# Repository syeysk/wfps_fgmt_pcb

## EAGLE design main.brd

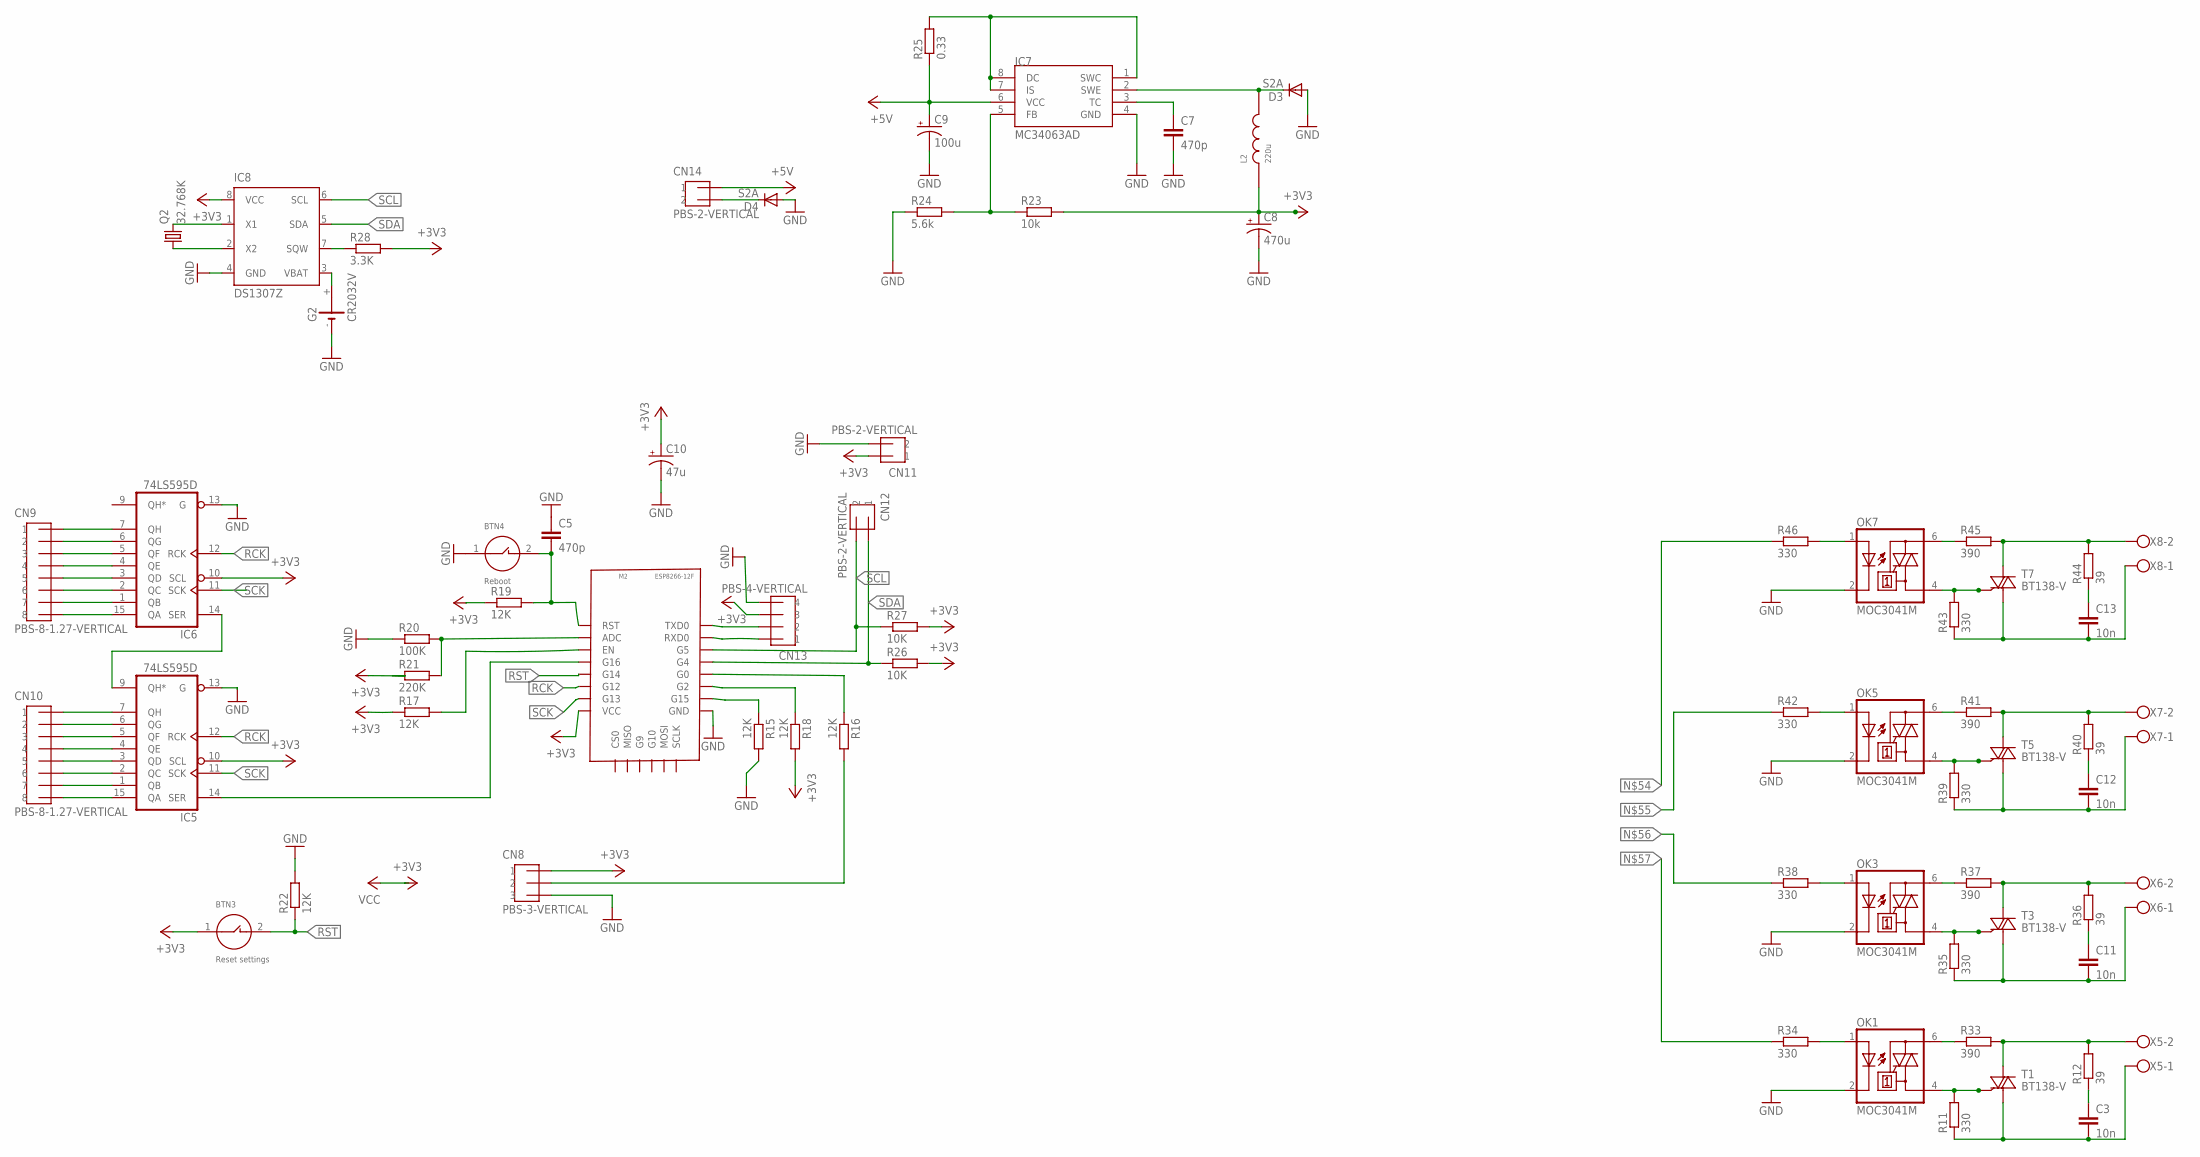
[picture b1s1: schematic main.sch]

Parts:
BTN3: Reset settings; BTN-6X4-SMD
BTN4: Reboot; BTN-6X4-SMD
C3, C11, C12, C13: 10n; C10B5
C5, C7: 470p; C0603
C8: 470u; D/7343-31W
C9: 100u; D/7343-31W
C10: 47u; CT3216
CN8: PBS-3-VERTICAL
CN9, CN10: PBS-8-1.27-VERTICAL
CN11, CN12, CN14: PBS-2-VERTICAL
CN13: PBS-4-VERTICAL
D3, D4: S2A; DO214AA
G2: CR2032V
IC5, IC6: 74LS595D; SO16
IC7: MC34063AD; SOIC8
IC8: DS1307Z; SOIC8
L2: 220u; INDUCTOR-5-10
M2: ESP8266-12F
OK1, OK3, OK5, OK7: MOC3041M; DIL06
Q2: 32.768K; TC38H
R11, R35, R39, R43: 330; 0411/12
R12, R36, R40, R44: 39; 0411/12
R15, R16, R17, R18, R19, R22: 12K; R0603
R20: 100K; R0603
R21: 220K; R0603
R23: 10k; R0603
R24: 5.6k; R0603
R25: 0.33; R0603
R26, R27: 10K; R0603
R28: 3.3K; R0603
R33, R37, R41, R45: 390; 0411/12
R34, R38, R42, R46: 330; R0603
T1, T3, T5, T7: BT138-V; TO220BV
X5, X6, X7, X8: W237-102

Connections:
+3V3: BTN3.1, C8.+, C10.- (+), CN8.P$1 (1), CN11.P$1 (1), CN13.P$3 (3), IC5.10 (SCL), IC5.16 (VCC), IC6.10 (SCL), IC6.16 (VCC), IC8.8 (VCC), L2.P$1 (1), M2.VCC, R17.1, R18.2, R19.1, R21.1, R23.2, R26.2, R27.2, R28.2
+5V: C9.+, CN14.P$1 (1), IC7.6 (VCC), R25.1
GND: BTN4.1, C5.1, C7.2, C8.-, C9.-, C10.+ (-), CN8.P$3 (3), CN11.P$2 (2), CN13.P$4 (4), D3.A, D4.A, G2.-, IC5.8 (GND), IC5.13 (G), IC6.8 (GND), IC6.13 (G), IC7.4 (GND), IC8.4 (GND), M2.GND, OK1.2 (C), OK3.2 (C), OK5.2 (C), OK7.2 (C), R15.2, R20.1, R22.2, R24.1
unnamed: OK1.1 (A), R34.2
unnamed: OK1.6 (A2), R33.1
unnamed: OK1.4 (A1), R11.2, T1.G
unnamed: R12.2, R33.2, T1.T2 (A2), X5.2
unnamed: C3.2, R11.1, T1.T1 (A1), X5.1
unnamed: C3.1, R12.1
unnamed: OK3.1 (A), R38.2
unnamed: M2.G15, R15.1
unnamed: M2.G2, R18.1
unnamed: M2.G0, R16.1
unnamed: CN8.P$2 (2), R16.2
unnamed: M2.EN, R17.2
unnamed: CN9.P$1 (1), IC6.7 (QH)
unnamed: CN9.P$2 (2), IC6.6 (QG)
unnamed: CN9.P$3 (3), IC6.5 (QF)
unnamed: CN9.P$4 (4), IC6.4 (QE)
unnamed: CN9.P$5 (5), IC6.3 (QD)
unnamed: CN9.P$6 (6), IC6.2 (QC)
unnamed: CN9.P$7 (7), IC6.1 (QB)
unnamed: CN9.P$8 (8), IC6.15 (QA)
unnamed: CN10.P$1 (1), IC5.7 (QH)
unnamed: CN10.P$2 (2), IC5.6 (QG)
unnamed: CN10.P$3 (3), IC5.5 (QF)
unnamed: CN10.P$4 (4), IC5.4 (QE)
unnamed: CN10.P$5 (5), IC5.3 (QD), R46.1
unnamed: CN10.P$6 (6), IC5.2 (QC), R42.1
unnamed: CN10.P$7 (7), IC5.1 (QB), R38.1
unnamed: CN10.P$8 (8), IC5.15 (QA), R34.1
unnamed: IC5.14 (SER), M2.G16
unnamed: IC5.9 (QH*), IC6.14 (SER)
unnamed: BTN4.2, C5.2, M2.RST, R19.2
unnamed: CN13.P$1 (1), M2.RXD0
unnamed: CN13.P$2 (2), M2.TXD0
unnamed: M2.ADC, R20.2, R21.2
unnamed: IC8.7 (SQW), R28.1
unnamed: IC8.1 (X1), Q2.2
unnamed: IC8.2 (X2), Q2.1
unnamed: G2.+, IC8.3 (VBAT)
unnamed: IC7.5 (FB), R23.1, R24.2
unnamed: IC7.1 (SWC), IC7.7 (IS), IC7.8 (DC), R25.2
unnamed: C7.1, IC7.3 (TC)
unnamed: D3.C, IC7.2 (SWE), L2.P$2
unnamed: CN14.P$2 (2), D4.C
unnamed: OK3.6 (A2), R37.1
unnamed: OK3.4 (A1), R35.2, T3.G
unnamed: R36.2, R37.2, T3.T2 (A2), X6.2
unnamed: C11.2, R35.1, T3.T1 (A1), X6.1
unnamed: C11.1, R36.1
unnamed: OK5.1 (A), R42.2
unnamed: OK5.6 (A2), R41.1
unnamed: OK5.4 (A1), R39.2, T5.G
unnamed: R40.2, R41.2, T5.T2 (A2), X7.2
unnamed: C12.2, R39.1, T5.T1 (A1), X7.1
unnamed: C12.1, R40.1
unnamed: OK7.1 (A), R46.2
unnamed: OK7.6 (A2), R45.1
unnamed: OK7.4 (A1), R43.2, T7.G
unnamed: R44.2, R45.2, T7.T2 (A2), X8.2
unnamed: C13.2, R43.1, T7.T1 (A1), X8.1
unnamed: C13.1, R44.1
RCK: IC5.12 (RCK), IC6.12 (RCK), M2.G12
RST: BTN3.2, M2.G14, R22.1
SCK: IC5.11 (SCK), IC6.11 (SCK), M2.G13
SCL: CN12.P$2 (2), IC8.6 (SCL), M2.G5, R27.1
SDA: CN12.P$1 (1), IC8.5 (SDA), M2.G4, R26.1

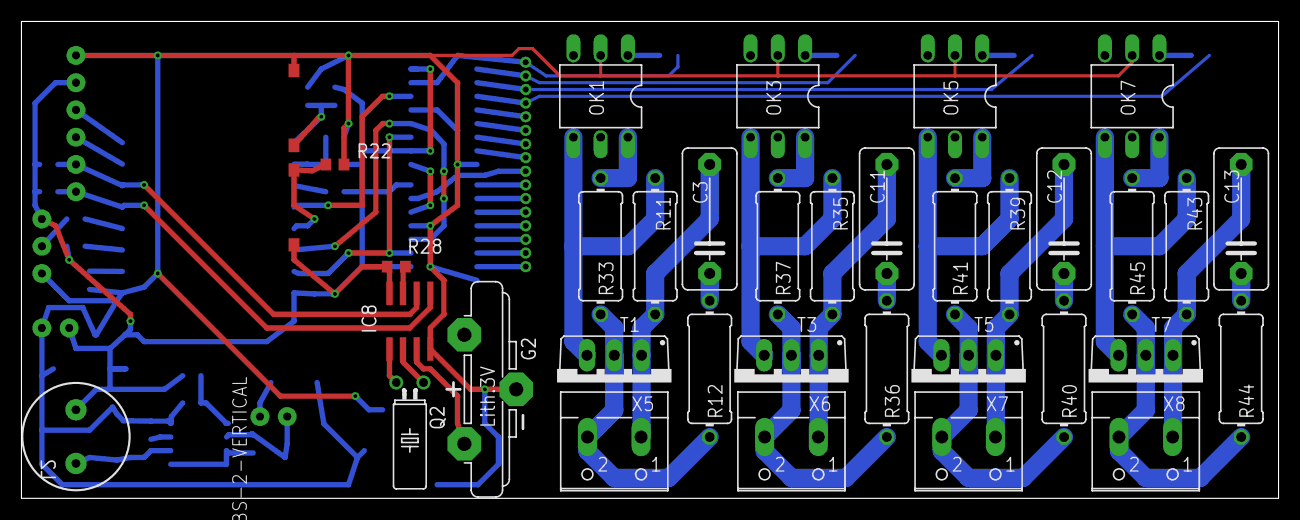
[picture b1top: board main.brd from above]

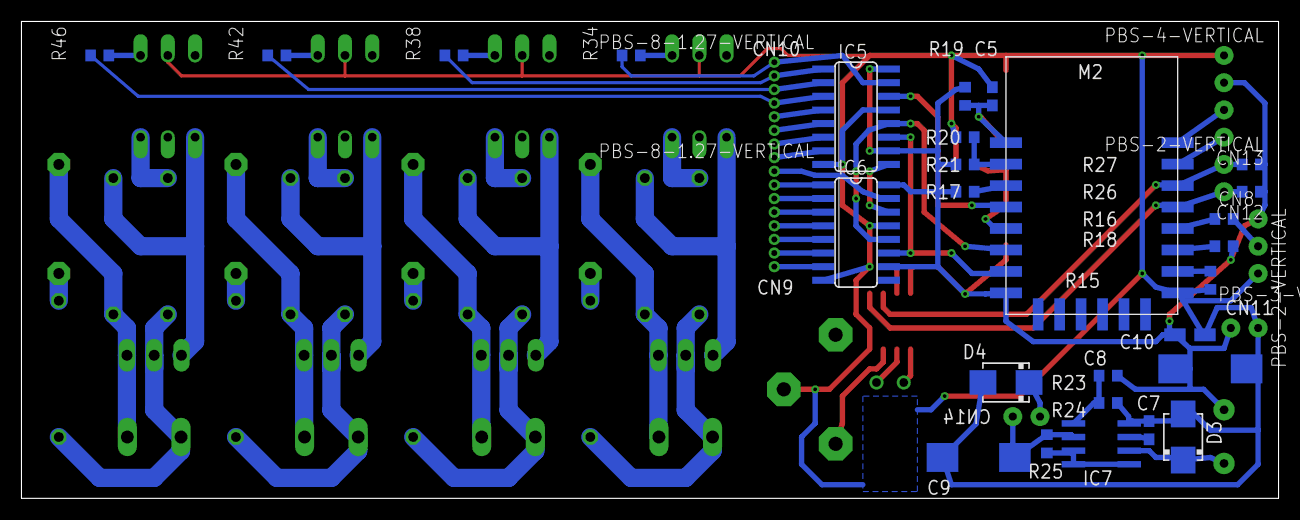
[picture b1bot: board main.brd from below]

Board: 2 copper layers, 117.1 x 44.4 mm, 70 parts (33 on the bottom side), 68 nets.

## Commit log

2018-09-20 submodule with eagle libs was added
2018-10-14 Value and name were changed. Eagle is 9.2.0
